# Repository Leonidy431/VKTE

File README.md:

# VKTE — инженерные проекты: Волга ГАЗ-2410 и УАЗ

Документация по дублирующим (резервным) электронным системам для
ГАЗ-2410 (двигатель ЗМЗ-402), интегрируемым в BlueOS, и по проекту
электропривода на базе УАЗа.

**Методология проекта:** см. [`CLOUD.md`](CLOUD.md) — 12-фазный подход с
научным базисом (PubMed/Scholar), многокритериальной оценкой (48
параметров), экспертным консенсусом (32 специалиста).

## Модули

- [`ignition/`](ignition/ignition_parts.md) — дублирующая система
  зажигания: штатный трамблёр + МПСЗ с силовым переключением между
  контурами.
- [`telemetry/`](telemetry/telemetry_rs485.md) — цифровая шина
  телеметрии на RS-485 (Modbus RTU) для сбора показаний датчиков
  (температура, ток, напряжение) и передачи их в BlueOS.
- [`plc/`](plc/prompt_for_claude.md) — готовый промт для Claude:
  список устройств и техзадание на программу ПЛК (Structured Text,
  OpenPLC), реализующую интерлок зажигания и опрос телеметрии.
- [`powerline/`](powerline/powerline_comm.md) — мост PLC (Power Line
  Communication) Ethernet <-> бортовая сеть 12В, для передачи данных
  без прокладки отдельного кабеля. Не путать с `plc/` (там PLC —
  Programmable Logic Controller).
- [`purchasing/`](purchasing/ozon_shopping_list.md) — консолидированный
  список покупок для Ozon/AliExpress по всем модулям с поисковыми
  запросами и техническими требованиями.
- [`engine/`](engine/engine_transmission.md) — проект УАЗ: выбор
  архитектуры привода (электромотор + КПП vs e-Axle vs синтез с
  раздаточной коробкой) для экспедиционных и водолазных задач.

Модули `ignition/`, `telemetry/`, `plc/`, `powerline/` рассчитаны на
совместную работу на Волге ГАЗ-2410: линия телеметрии (RS-485, витая
пара) прокладывается отдельно от проводки зажигания и МПСЗ, чтобы
избежать взаимных наводок. Модуль `engine/` относится к отдельному
проекту (УАЗ) и пока не связан с остальными.

Каждый модуль состоит из генератора (`generate_*.py`), формирующего
итоговый markdown-документ, и самого сгенерированного файла.

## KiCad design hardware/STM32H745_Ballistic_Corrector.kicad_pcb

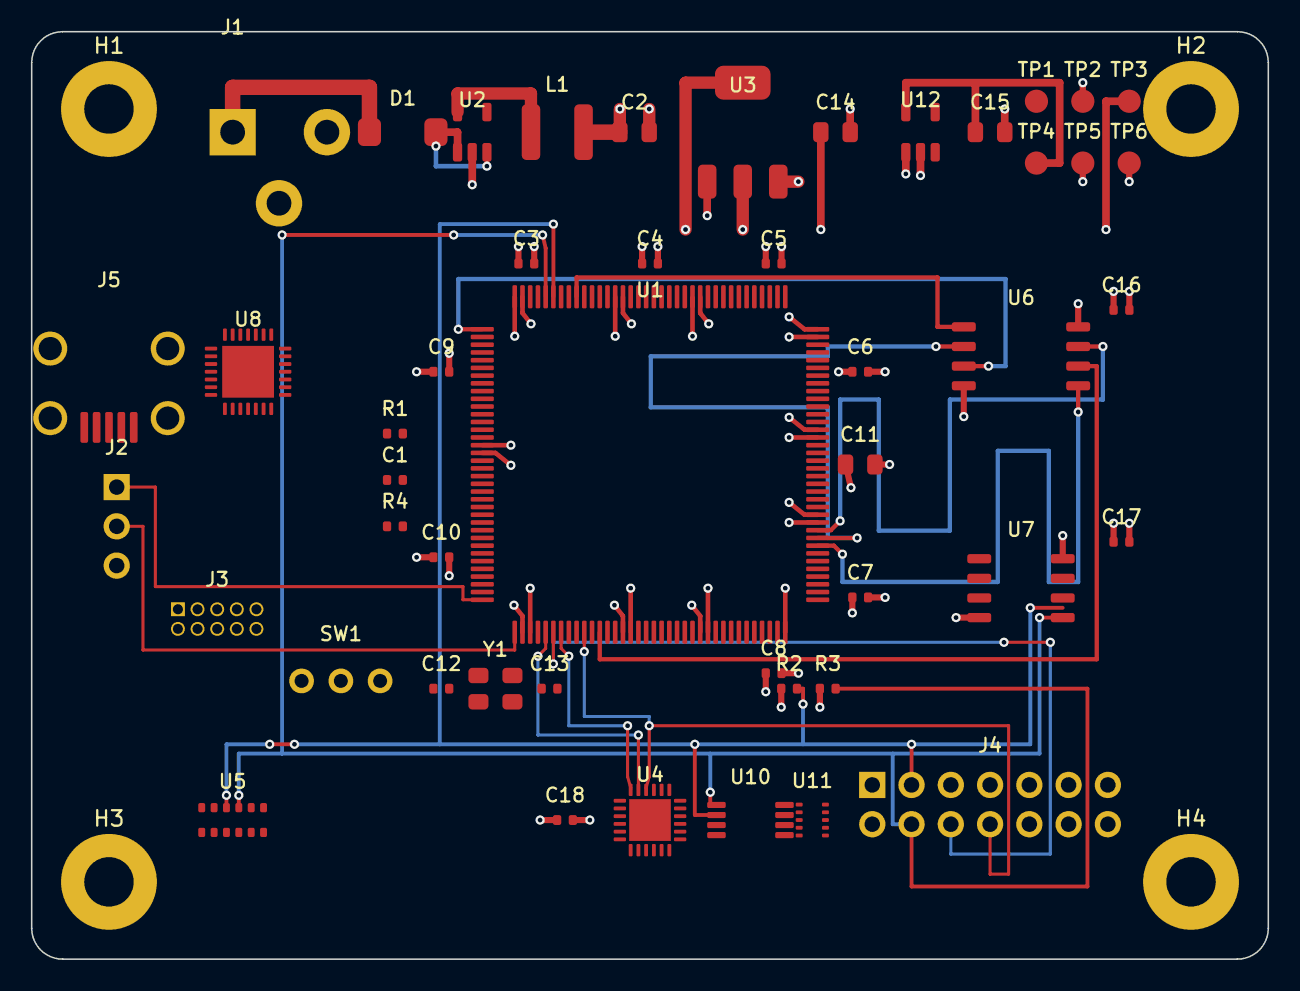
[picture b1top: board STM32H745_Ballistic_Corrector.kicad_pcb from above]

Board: 4 copper layers, 80.0 x 60.0 mm, 52 parts (0 on the bottom side), 25 nets.

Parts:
C1, C3, C4, C5, C6, C7, C8, C9, C10, C16, C17, C18: 100nF; C_0402
C2, C11, C14, C15: 10uF; C_0805
C12, C13: 12pF 1%; C_0402
D1: 1N5819 SMA; D_SMA
H1, H2, H3, H4: M3; MountingHole_3.2mm_M3_Pad_Via
J1: 12V_IN; BarrelJack_5.5x2.1mm
J2: UART_DBG; PinHeader_1x03
J3: SWD; PinHeader_2x05
J4: SENSOR_14P; PinHeader_2x07
J5: USB_MINI_B; USB_Mini-B
L1: 4.7uH; L_4x4mm
R1, R2, R3, R4: 10k; R_0402
SW1: BOOT0; SW_Slide
TP1: VCC_12V; TestPoint_Pad_1.5mm
TP2: VCC_5V; TestPoint_Pad_1.5mm
TP3: VCC_3V3; TestPoint_Pad_1.5mm
TP4: VCC_1V8; TestPoint_Pad_1.5mm
TP5, TP6: GND; TestPoint_Pad_1.5mm
U1: STM32H745ZIT6; LQFP-144_20x20mm_P0.5mm
U2: TPS62133A; SOT-23-5
U3: LDO_3V3_500mA; SOT-223
U4: ICM-20689; QFN-24_4x4mm_P0.5mm
U5: VL53L0X; ST_VL53L0X
U6: W25Q128JV; SOIC-8_5.23x5.23mm_P1.27mm
U7: AT24C256C; SOIC-8_3.9x4.9mm_P1.27mm
U8: CP2102N; QFN-28_5x5mm_P0.5mm
U10: MCP9808; MSOP-8_3x3mm_P0.65mm
U11: BMP390; Bosch_LGA-10
U12: LDO_1V8_200mA; SOT-23-5
Y1: 8MHz; Crystal_SMD_3225-4Pin

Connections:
BOOT0: R4.1, SW1.2, U1.138
GND: C1.2, C2.2, C3.2, C4.2, C5.2, C6.2, C7.2, C8.2, C9.2, C10.2, C11.2, C12.2, C13.2, C14.2, C15.2, C16.2, C17.2, C18.2, H1.1, H2.1, H3.1, H4.1, J1.2, J1.3, J2.3, J3.3, J3.5, J3.9, J4.2, J4.14, J5.5, J5.S1, J5.S2, J5.S3, J5.S4, R4.2, SW1.3, TP5.1, TP6.1, U1.16, U1.38, U1.51, U1.61, U1.83, U1.94, U1.107, U1.120, U1.130, U1.143, U2.2, U3.1, U4.18, U4.25, U5.3, U5.4, U5.6, U5.12, U6.4, U7.1, U7.2, U7.3, U7.4, U7.7, U8.29, U10.4, U10.5, U10.6, U10.7, U12.2, Y1.2, Y1.4
I2C1_SCL: J4.3, R2.2, U1.139, U5.10, U7.6, U10.2
I2C1_SDA: J4.4, R3.2, U1.140, U5.9, U7.5, U10.1
NRST: C1.1, J3.10, R1.2, U1.25
PWR_12V_RAW: D1.1, J1.1
PWR_SW: L1.1, U2.5
QSPI_CLK: U1.48, U6.6
QSPI_CS: U1.136, U6.1
QSPI_D0: U1.80, U6.5
QSPI_D1: U1.81, U6.2
QSPI_D2: U1.1, U6.3
QSPI_D3: U1.82, U6.7
SPI1_CLK: J4.5, U1.41, U4.23
SPI1_CS_IMU: J4.8, U1.46, U4.22
SPI1_MISO: J4.6, U1.42
SPI1_MOSI: J4.7, U1.43, U4.24
UART2_RX: J2.2, U1.37
UART2_TX: J2.1, U1.36
USB_DM: J5.2, U1.103
USB_DP: J5.3, U1.104
VCC_1V8: C15.1, TP4.1, U12.5
VCC_3V3: C3.1, C4.1, C5.1, C6.1, C7.1, C8.1, C9.1, C10.1, C11.1, C14.1, C16.1, C17.1, C18.1, J3.1, J4.1, R1.1, R2.1, R3.1, SW1.1, TP3.1, U1.17, U1.39, U1.52, U1.62, U1.72, U1.84, U1.95, U1.108, U1.121, U1.131, U1.144, U3.2, U3.4, U4.8, U4.13, U5.1, U5.11, U6.8, U7.8, U10.8
VCC_5V: C2.1, J5.1, L1.2, TP2.1, U3.3, U12.1
VCC_12V: D1.2, TP1.1, U2.1, U2.3

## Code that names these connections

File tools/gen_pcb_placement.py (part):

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# Pin numbers follow the standard STM32 LQFP144 arrangement; VERIFY against
# the STM32H745ZIT6 datasheet at netlist import (VCAP/analog pins left open).
U1_NETS = {
    1: "QSPI_D2",            # PE2 / QUADSPI_BK1_IO2
    16: "GND", 17: "VCC_3V3",
    25: "NRST",
    36: "UART2_TX", 37: "UART2_RX",      # PA2 / PA3
    38: "GND", 39: "VCC_3V3",
    41: "SPI1_CLK", 42: "SPI1_MISO", 43: "SPI1_MOSI",  # PA5-PA7
    46: "SPI1_CS_IMU",       # PB0
    48: "QSPI_CLK",          # PB2
    51: "GND", 52: "VCC_3V3", 61: "GND", 62: "VCC_3V3", 72: "VCC_3V3",
    80: "QSPI_D0", 81: "QSPI_D1", 82: "QSPI_D3",       # PD11-PD13
    83: "GND", 84: "VCC_3V3", 94: "GND", 95: "VCC_3V3",
    103: "USB_DM", 104: "USB_DP",        # PA11 / PA12
    107: "GND", 108: "VCC_3V3",
    120: "GND", 121: "VCC_3V3", 130: "GND", 131: "VCC_3V3",
    136: "QSPI_CS",          # PB6 / QUADSPI_BK1_NCS
    138: "BOOT0",
    139: "I2C1_SCL", 140: "I2C1_SDA",    # PB8 / PB9
    143: "GND", 144: "VCC_3V3",
}

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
